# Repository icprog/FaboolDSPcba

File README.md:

#FABOOL Laser DS PCBA
- Product page: https://www.smartdiys.cc/fabool-laser-ds/
- Shop page: https://shop.smartdiys.cc/collections/80w-co2-laser-cutter-and-engraver

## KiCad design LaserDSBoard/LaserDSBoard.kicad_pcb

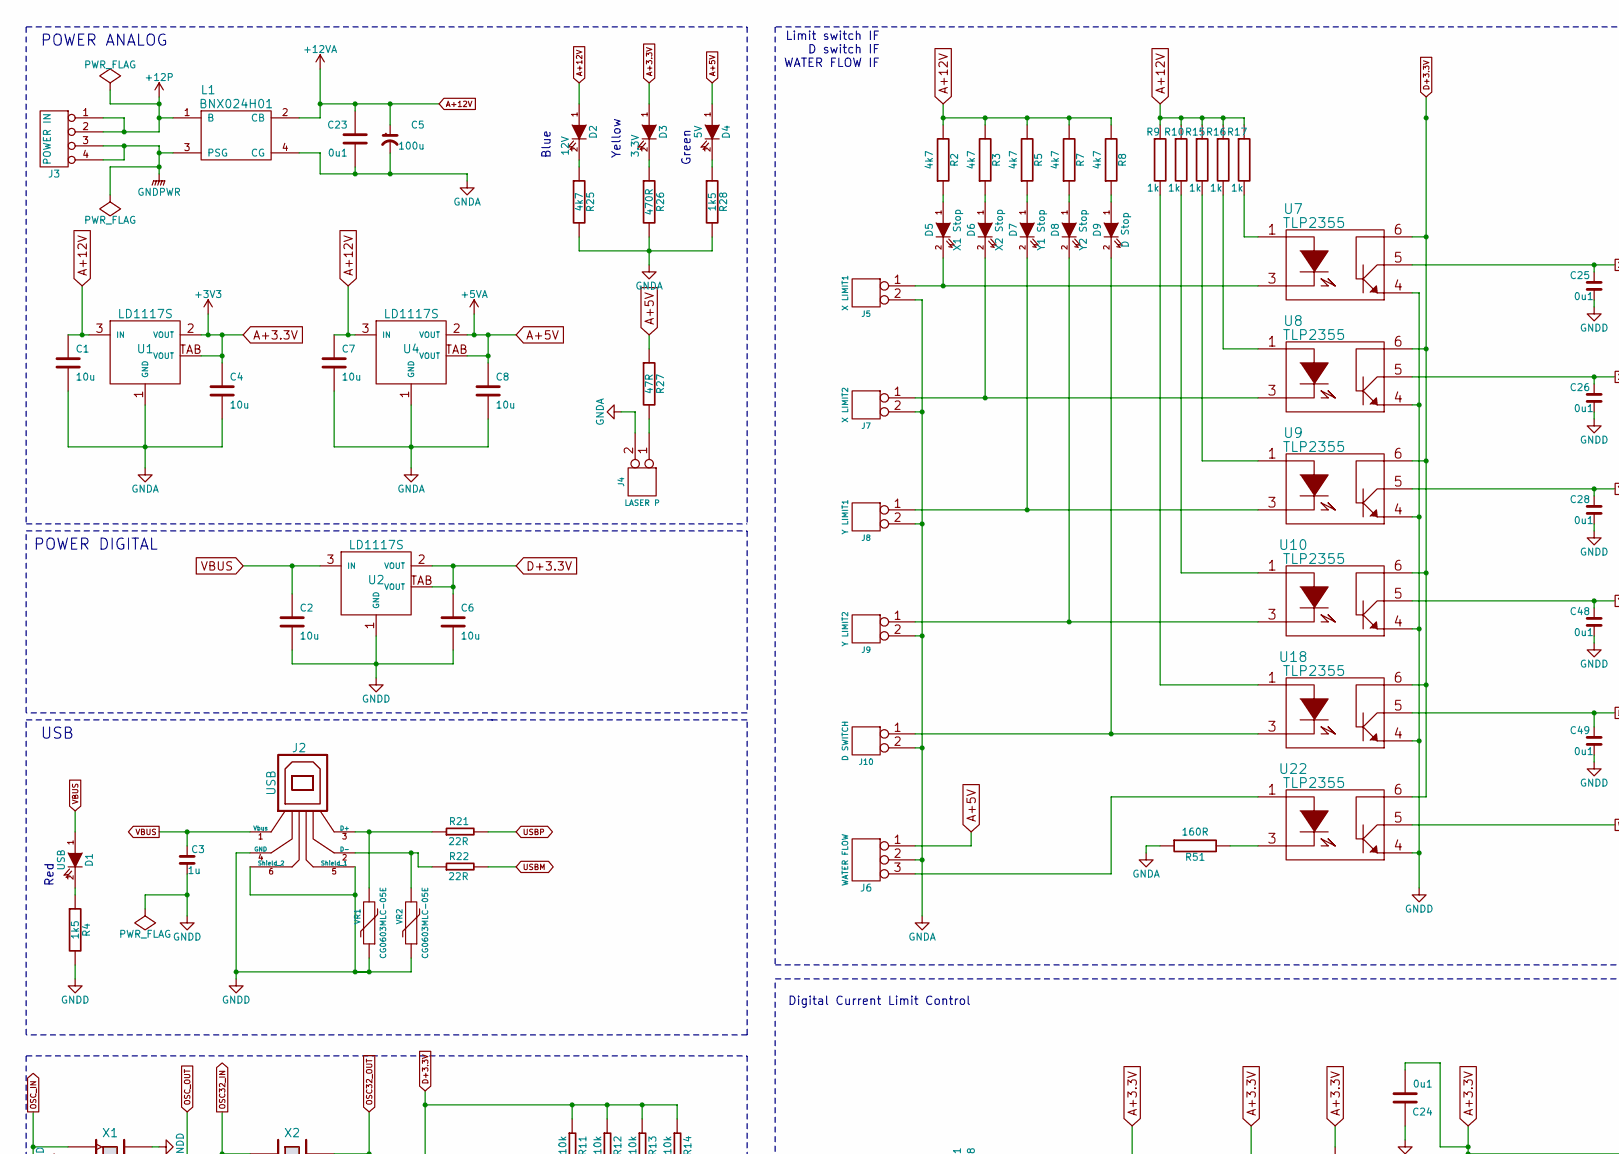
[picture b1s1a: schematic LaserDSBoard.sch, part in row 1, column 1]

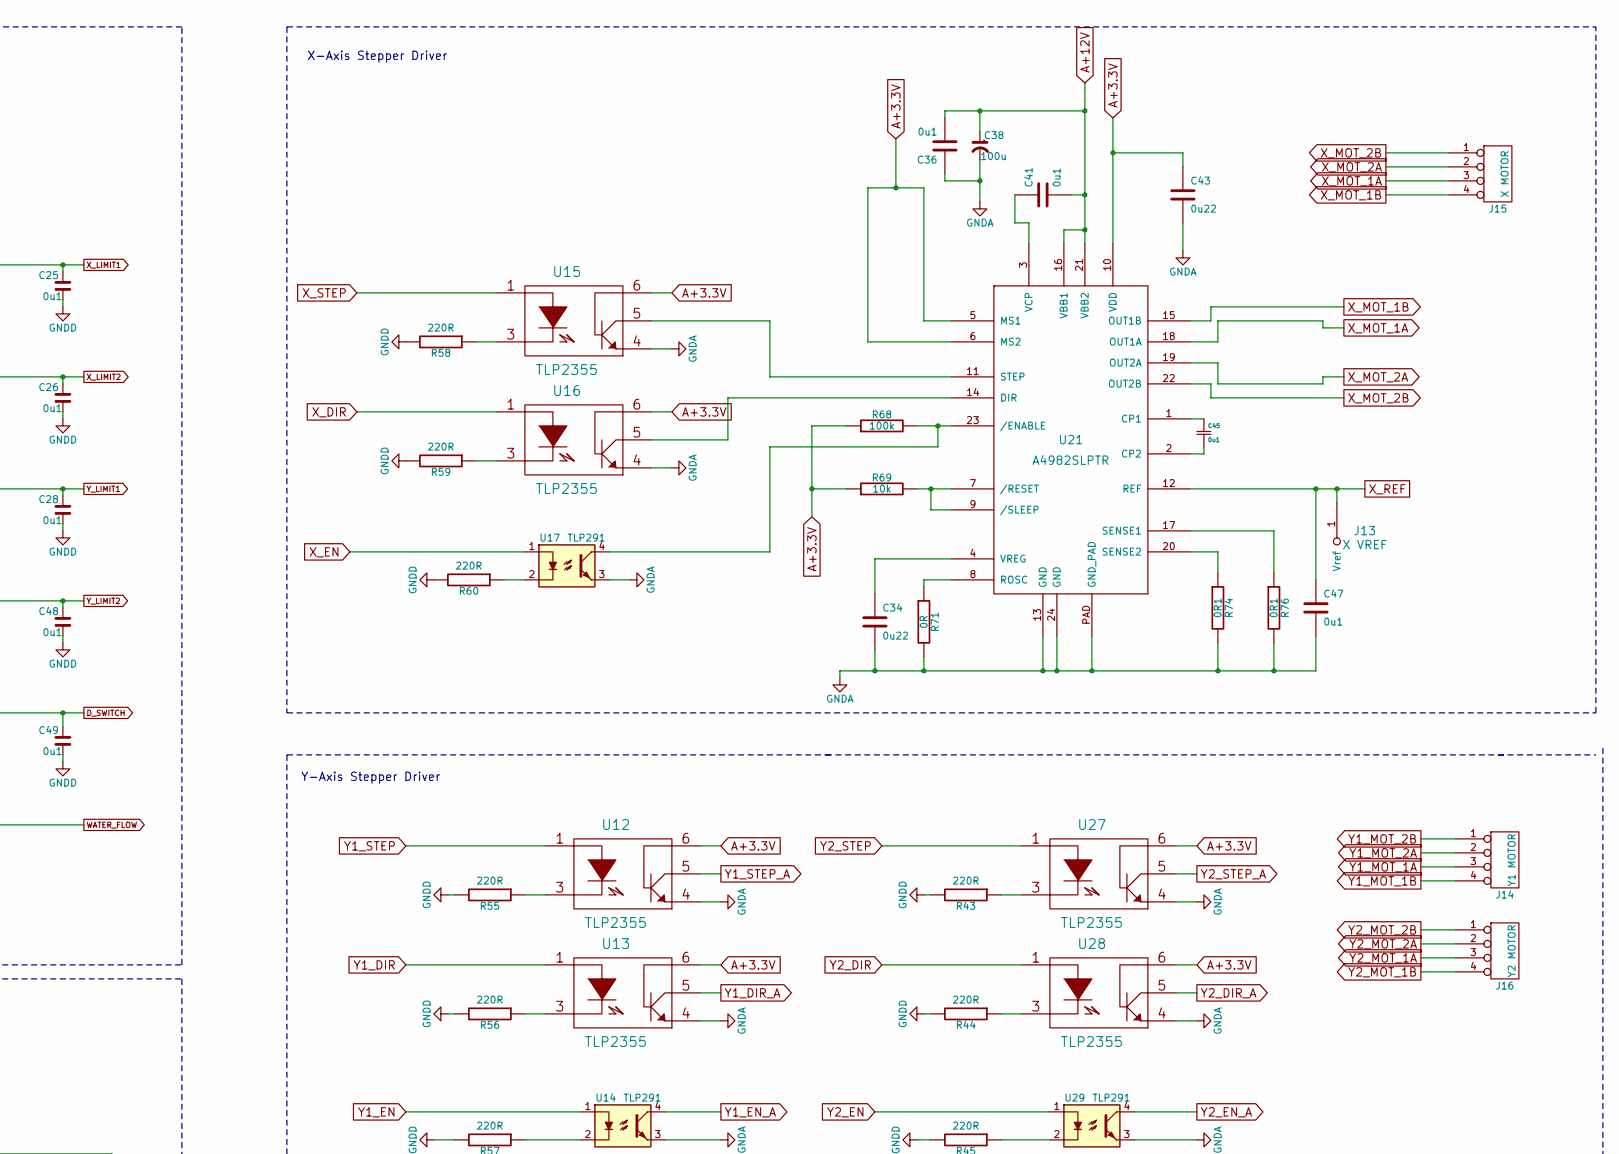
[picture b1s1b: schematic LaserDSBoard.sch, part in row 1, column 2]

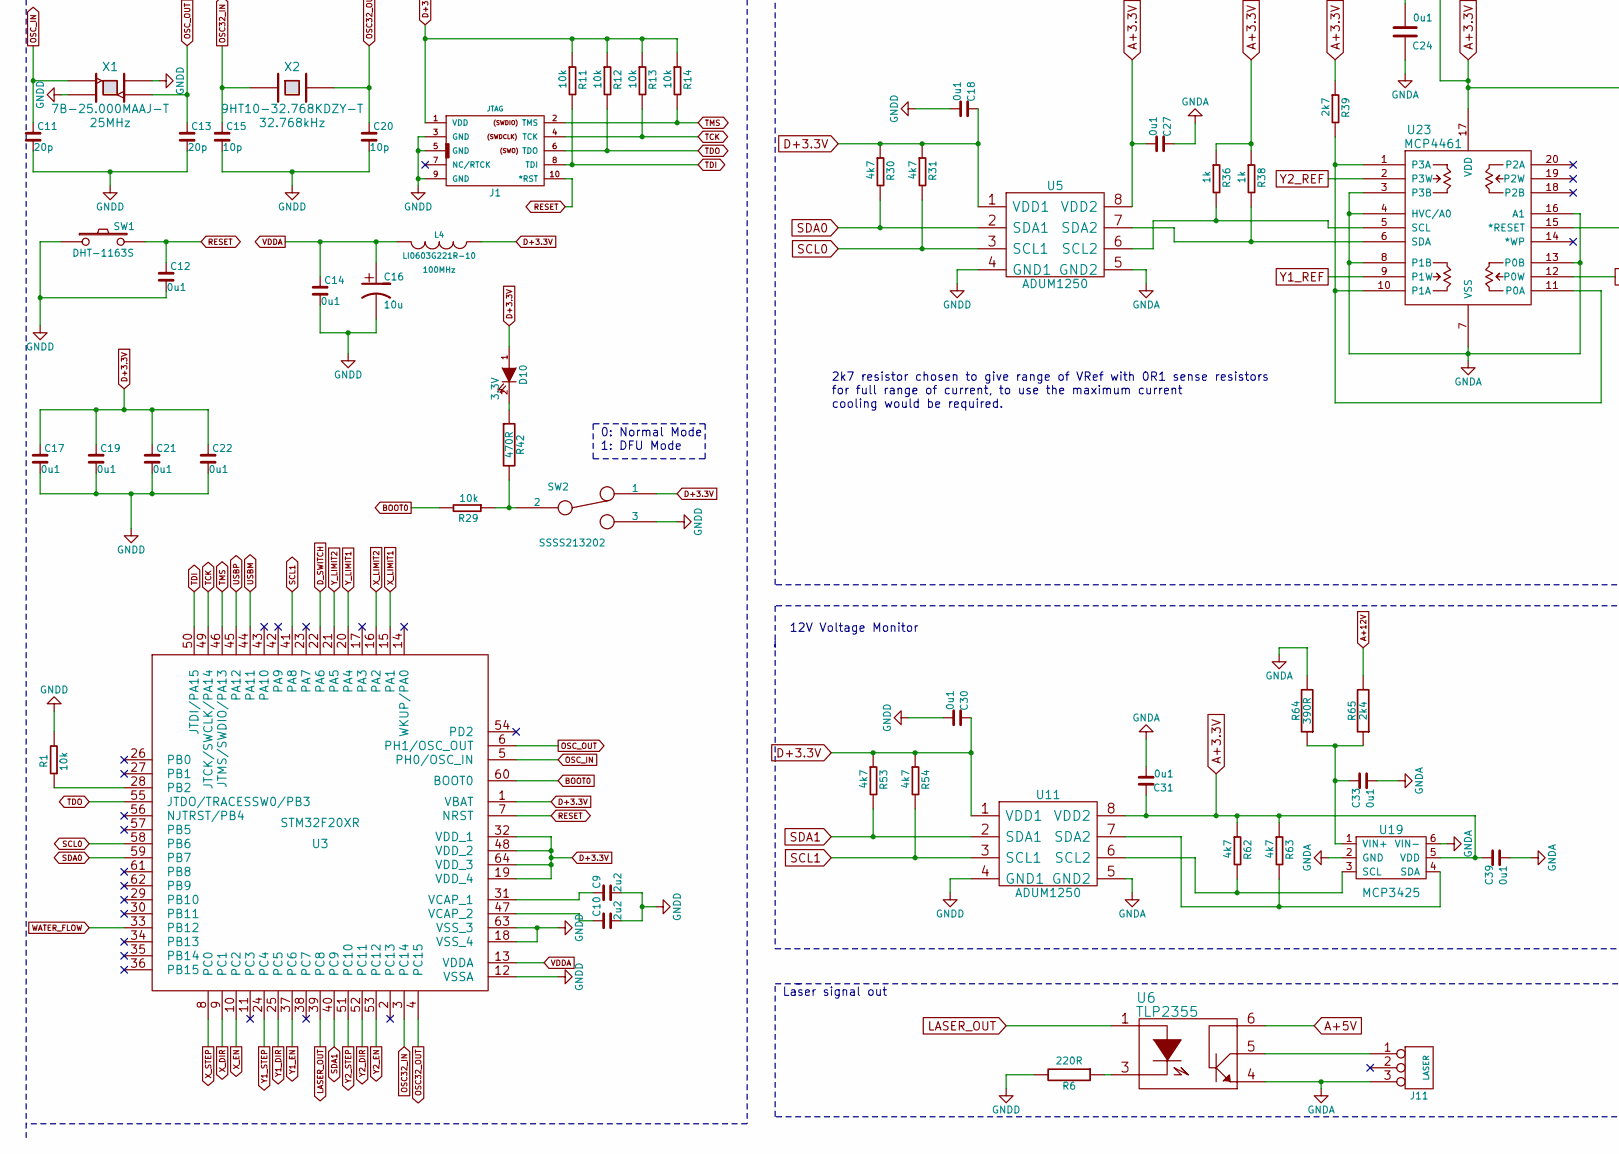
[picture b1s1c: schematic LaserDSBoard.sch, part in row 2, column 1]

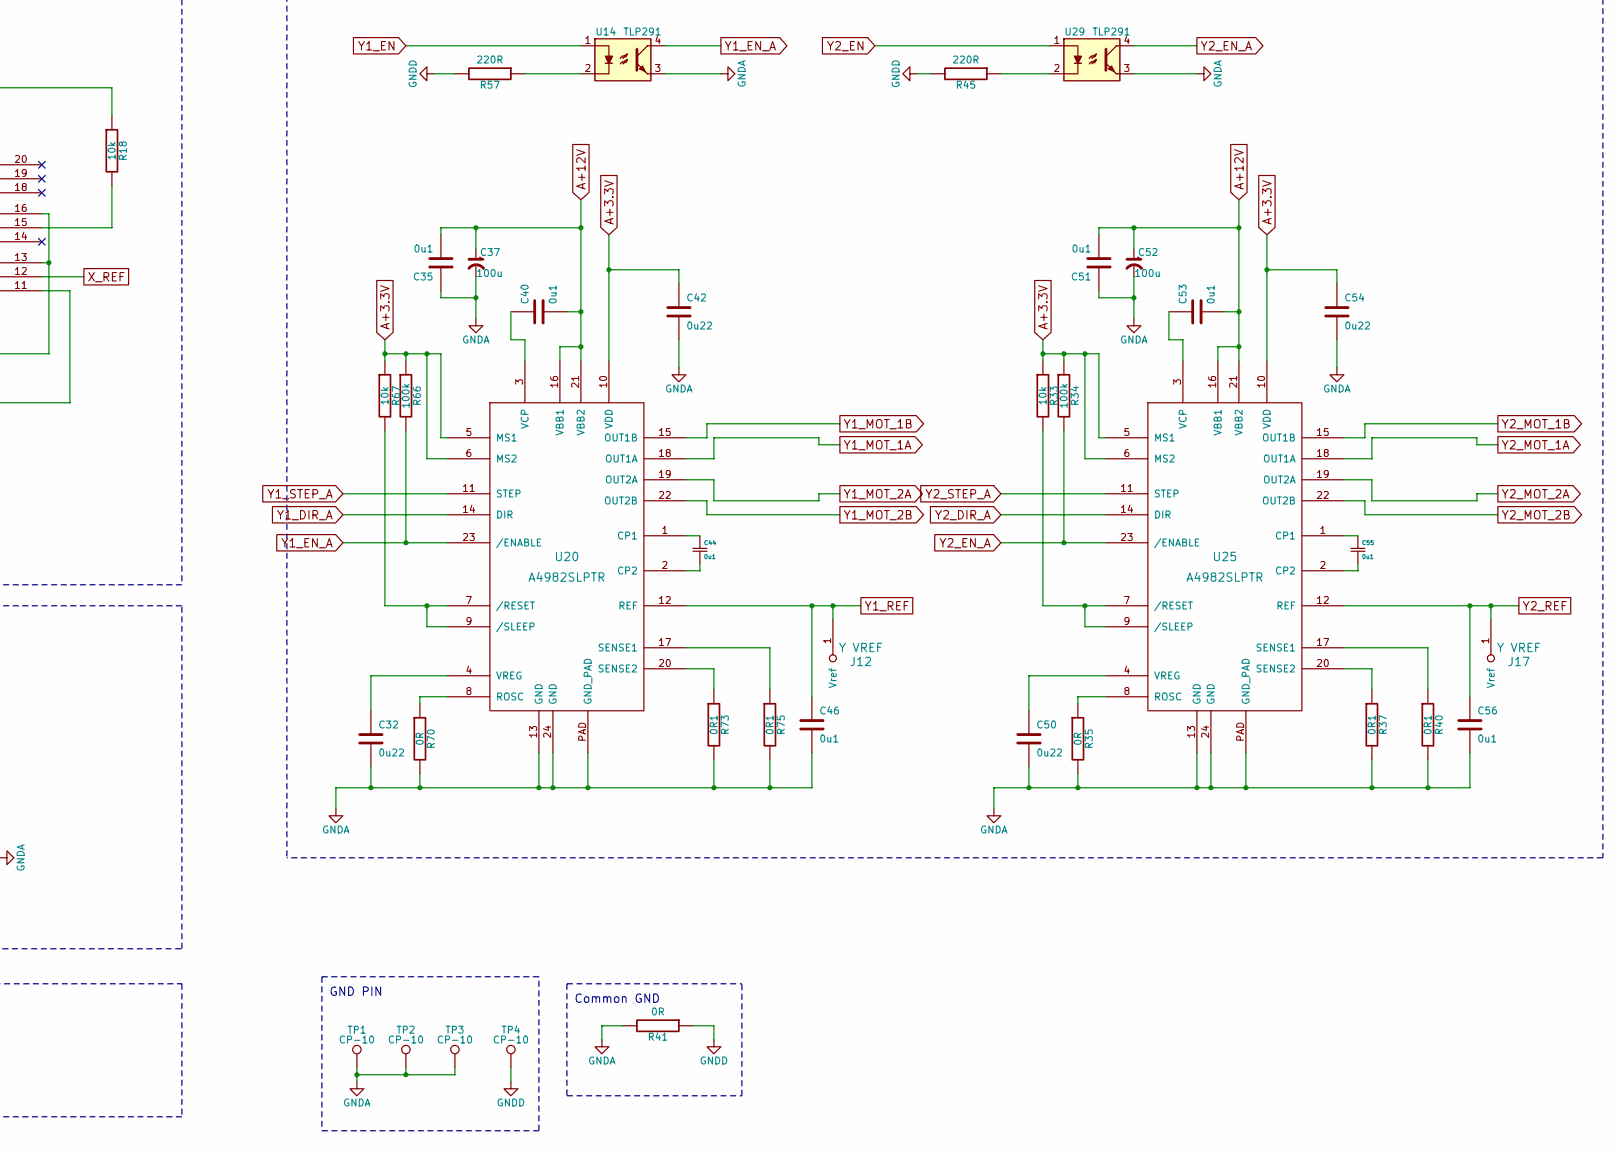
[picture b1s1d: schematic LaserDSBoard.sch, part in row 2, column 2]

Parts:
C1, C2, C4, C6, C7, C8, C16: 10u; C_0805
C3: 1u; C_0603
C5, C37, C38, C52: 100u; CP_Elec_6.3x7.7
C9, C10: 2u2; C_0603
C11, C13: 20p; C_0603
C12, C14, C17, C18, C19, C21, C22, C23, C24, C25, C26, C27, C28, C30, C31, C33, C35, C36, C39, C40, C41, C44, C45, C46, C47, C48, C49, C51, C53, C55, C56: 0u1; C_0805
C15, C20: 10p; C_0603
C32, C34, C42, C43, C50, C54: 0u22; C_0603
D1: USB; D_0805
D2: 12V; D_0805
D3, D10: 3.3V; D_0805
D4: 5V; D_0805
D5: X1 Stop; D_0805
D6: X2 Stop; D_0805
D7: Y1 Stop; D_0805
D8: Y2 Stop; D_0805
D9: D Stop; D_0805
J1: JTAG; Pin_Header_Straight_2x05_Pitch1.27mm
J2: USB; USB_B
J3: POWER IN; VH-4
J4: LASER P; B2B-XH-A
J5: X LIMIT1; B2B-XH-A
J6: WATER FLOW; B3B-XH-A
J7: X LIMIT2; B2B-XH-A
J8: Y LIMIT1; B2B-XH-A
J9: Y LIMIT2; B2B-XH-A
J10: D SWITCH; B2B-XH-A
J11: LASER; B3B-XH-A
J12, J17: Y VREF; Pin_Header_Straight_1x01_Pitch1.00mm
J13: X VREF; Pin_Header_Straight_1x01_Pitch1.00mm
J14: Y1 MOTOR; VH-4
J15: X MOTOR; VH-4
J16: Y2 MOTOR; VH-4
L1: BNX024H01
L4: LI0603G221R-10; R_0603
R1, R11, R12, R13, R14, R18, R29, R33, R67, R69: 10k; R_0603
R2, R3, R5, R7, R8, R25, R30, R31, R53, R54, R62, R63: 4k7; R_0603
R4, R28: 1k5; R_0603
R6, R43, R44, R45, R55, R56, R57, R58, R59, R60: 220R; R_1206
R9, R10, R15, R16, R17, R36, R38: 1k; R_0603
R21, R22: 22R; R_0603
R26, R42: 470R; R_0603
R27: 47R; R_0603
R34, R66, R68: 100k; R_0603
R35, R41, R70, R71: 0R; R_1206
R37, R40, R73, R74, R75, R76: 0R1; R_1206
R39: 2k7; R_0603
R51: 160R; R_1206
R64: 390R; R_0603
R65: 2k4; R_0603
SW1: DHT-1163S
SW2: SSSS213202
TP1, TP2, TP3, TP4: CP-10; Pin_Header_Straight_1x01_Pitch2.54mm
U1, U2, U4: LD1117S; LD1117S33TR
U3: STM32F20XR; LQFP-64_10x10mm_Pitch0.5mm
U5, U11: ADUM1250
U6, U7, U8, U9, U10, U12, U13, U15, U16, U18, U22, U27, U28: TLP2355
U14, U17, U29: TLP291; TLP291(SE
U19: MCP3425
U20, U21, U25: A4982SLPTR
U23: MCP4461; TSSOP-20_4.4x6.5mm_P0.65mm
VR1, VR2: CG0603MLC-05E; C_0603
X1: 7B-25.000MAAJ-T; Oscillator_SMD_Fordahl_DFAS15-4pin_5.0x3.2mm
X2: 9HT10-32.768KDZY-T; C_1206

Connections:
+12P: J3.1, J3.2, L1.1 (B)
A+3.3V: C4.1, C24.2, C27.2, C31.1, C39.1, C42.1, C43.1, C54.1, D3.1 (A), R18.1, R33.1, R34.1, R36.1, R38.1, R39.1, R62.1, R63.1, R66.1, R67.1, R68.1, R69.1, U1.2 (VOUT), U1.TAB (VOUT), U5.8 (VDD2), U11.8 (VDD2), U12.6, U13.6, U15.6, U16.6, U19.5 (VDD), U20.5 (MS1), U20.6 (MS2), U20.10 (VDD), U21.5 (MS1), U21.6 (MS2), U21.10 (VDD), U23.17 (VDD), U25.5 (MS1), U25.6 (MS2), U25.10 (VDD), U27.6, U28.6
A+5V: C8.1, D4.1 (A), J6.1, R27.1, U4.2 (VOUT), U4.TAB (VOUT), U6.6
A+12V: C1.1, C5.1, C7.1, C23.1, C35.2, C36.2, C37.1, C38.1, C40.2, C41.2, C51.2, C52.1, C53.2, D2.1 (A), L1.2 (CB), R2.2, R3.2, R5.2, R7.2, R8.2, R9.1, R10.1, R15.1, R16.1, R17.1, R65.2, U1.3 (IN), U4.3 (IN), U20.16 (VBB1), U20.21 (VBB2), U21.16 (VBB1), U21.21 (VBB2), U25.16 (VBB1), U25.21 (VBB2)
BOOT0: R29.2, U3.60 (BOOT0)
D+3.3V: C6.1, C17.1, C18.1, C19.1, C21.1, C22.1, C30.1, D10.1 (A), J1.1 (VDD), L4.1, R11.1, R12.1, R13.1, R14.1, R30.1, R31.1, R53.1, R54.1, SW2.1, U2.2 (VOUT), U2.TAB (VOUT), U3.1 (VBAT), U3.19 (VDD_4), U3.32 (VDD_1), U3.48 (VDD_2), U3.64 (VDD_3), U5.1 (VDD1), U7.6, U8.6, U9.6, U10.6, U11.1 (VDD1), U18.6, U22.6
D_SWITCH: C49.1, U3.22 (PA6), U18.5
GNDA: C1.2, C4.2, C5.2, C7.2, C8.2, C23.2, C24.1, C27.1, C31.2, C32.2, C33.2, C34.2, C35.1, C36.1, C37.2, C38.2, C39.2, C42.2, C43.2, C46.2, C47.2, C50.2, C51.1, C52.2, C54.2, C56.2, J4.2 (PM), J5.2 (PM), J6.2 (PM), J7.2 (PM), J8.2 (PM), J9.2 (PM), J10.2 (PM), J11.3, L1.4 (CG), R25.2, R26.2, R28.2, R35.2, R37.2, R40.2, R41.2, R51.1, R64.2, R70.2, R71.2, R73.2, R74.2, R75.2, R76.2, TP1.1, TP2.1, TP3.1, U1.1 (GND), U4.1 (GND), U5.5 (GND2), U6.4, U11.5 (GND2), U12.4, U13.4, U14.3, U15.4, U16.4, U17.3, U19.2 (GND), U19.6 (VIN-), U20.13 (GND), U20.24 (GND), U20.PAD (GND_PAD), U21.13 (GND), U21.24 (GND), U21.PAD (GND_PAD), U23.3 (P3B), U23.4 (HVC/A0), U23.7 (VSS), U23.8 (P1B), U23.13 (P0B), U23.16 (A1), U25.13 (GND), U25.24 (GND), U25.PAD (GND_PAD), U27.4, U28.4, U29.3
GNDD: C2.2, C3.2, C6.2, C9.2, C10.2, C11.2, C12.2, C13.2, C14.2, C15.2, C16.2, C17.2, C18.2, C19.2, C20.2, C21.2, C22.2, C25.2, C26.2, C28.2, C30.2, C48.2, C49.2, J1.3 (GND), J1.5 (GND), J1.9 (GND), J2.4 (GND), J2.5 (Shield_1), J2.6 (Shield_2), R1.2, R4.2, R6.2, R41.1, R43.2, R44.2, R45.2, R55.2, R56.2, R57.2, R58.2, R59.2, R60.2, SW1.1, SW2.3, TP4.1, U2.1 (GND), U3.12 (VSSA), U3.18 (VSS_4), U3.63 (VSS_3), U5.4 (GND1), U7.4, U8.4, U9.4, U10.4, U11.4 (GND1), U18.4, U22.4, VR1.1, VR2.1, X1.2, X1.4
GNDPWR: J3.3, J3.4, L1.3 (PSG)
LASER_OUT: U3.39 (PC8), U6.1
unnamed: C9.1, U3.31 (VCAP_1)
unnamed: C10.1, U3.47 (VCAP_2)
unnamed: C32.1, U20.4 (VREG)
unnamed: C33.1, R64.1, R65.1, U19.1 (VIN+)
unnamed: C34.1, U21.4 (VREG)
unnamed: C40.1, U20.3 (VCP)
unnamed: C41.1, U21.3 (VCP)
unnamed: C44.1, U20.1 (CP1)
unnamed: C44.2, U20.2 (CP2)
unnamed: C45.1, U21.1 (CP1)
unnamed: C45.2, U21.2 (CP2)
unnamed: C50.1, U25.4 (VREG)
unnamed: C53.1, U25.3 (VCP)
unnamed: C55.1, U25.1 (CP1)
unnamed: C55.2, U25.2 (CP2)
unnamed: D1.2 (K), R4.1
unnamed: D2.2 (K), R25.1
unnamed: D3.2 (K), R26.1
unnamed: D4.2 (K), R28.1
unnamed: D5.1 (A), R2.1
unnamed: D5.2 (K), J5.1, U7.3
unnamed: D6.1 (A), R3.1
unnamed: D6.2 (K), J7.1, U8.3
unnamed: D7.1 (A), R5.1
unnamed: D7.2 (K), J8.1, U9.3
unnamed: D8.1 (A), R7.1
unnamed: D8.2 (K), J9.1, U10.3
unnamed: D9.1 (A), R8.1
unnamed: D9.2 (K), J10.1, U18.3
unnamed: D10.2 (K), R42.1
unnamed: J2.2 (D-), R22.1, VR2.2
unnamed: J2.3 (D+), R21.1, VR1.2
unnamed: J4.1, R27.2
unnamed: J6.3, U22.1
unnamed: J11.1, U6.5
unnamed: R1.1, U3.28 (PB2)
unnamed: R6.1, U6.3
unnamed: R9.2, U18.1
unnamed: R10.2, U10.1
unnamed: R15.2, U9.1
unnamed: R16.2, U8.1
unnamed: R17.2, U7.1
unnamed: R18.2, U23.15 (*RESET)
unnamed: R29.1, R42.2, SW2.2
unnamed: R33.2, U25.7 (/RESET), U25.9 (/SLEEP)
unnamed: R35.1, U25.8 (ROSC)
unnamed: R36.2, U5.6 (SCL2), U23.5 (SCL)
unnamed: R37.1, U25.20 (SENSE2)
unnamed: R38.2, U5.7 (SDA2), U23.6 (SDA)
unnamed: R39.2, U23.1 (P3A), U23.10 (P1A), U23.11 (P0A)
unnamed: R40.1, U25.17 (SENSE1)
unnamed: R43.1, U27.3
unnamed: R44.1, U28.3
unnamed: R45.1, U29.2
unnamed: R51.2, U22.3
unnamed: R55.1, U12.3
unnamed: R56.1, U13.3
unnamed: R57.1, U14.2
unnamed: R58.1, U15.3
unnamed: R59.1, U16.3
unnamed: R60.1, U17.2
unnamed: R62.2, U11.6 (SCL2), U19.3 (SCL)
unnamed: R63.2, U11.7 (SDA2), U19.4 (SDA)
unnamed: R67.2, U20.7 (/RESET), U20.9 (/SLEEP)
unnamed: R68.2, U17.4, U21.23 (/ENABLE)
unnamed: R69.2, U21.7 (/RESET), U21.9 (/SLEEP)
unnamed: R70.1, U20.8 (ROSC)
unnamed: R71.1, U21.8 (ROSC)
unnamed: R73.1, U20.20 (SENSE2)
unnamed: R74.1, U21.20 (SENSE2)
unnamed: R75.1, U20.17 (SENSE1)
unnamed: R76.1, U21.17 (SENSE1)
unnamed: U15.5, U21.11 (STEP)
unnamed: U16.5, U21.14 (DIR)
OSC32_IN: C15.1, U3.3 (PC14), X2.1
OSC32_OUT: C20.1, U3.4 (PC15), X2.2
OSC_IN: C11.1, U3.5 (PH0/OSC_IN), X1.1
OSC_OUT: C13.1, U3.6 (PH1/OSC_OUT), X1.3
RESET: C12.1, J1.10 (*RST), SW1.2, U3.7 (NRST)
SCL0: R31.2, U3.58 (PB6), U5.3 (SCL1)
SCL1: R54.2, U3.41 (PA8), U11.3 (SCL1)
SDA0: R30.2, U3.59 (PB7), U5.2 (SDA1)
SDA1: R53.2, U3.40 (PC9), U11.2 (SDA1)
TCK: J1.4 (TCK), R13.2, U3.49 (JTCK/SWCLK/PA14)
TDI: J1.8 (TDI), R11.2, U3.50 (JTDI/PA15)
TDO: J1.6 (TDO), R12.2, U3.55 (JTDO/TRACESSW0/PB3)
TMS: J1.2 (TMS), R14.2, U3.46 (JTMS/SWDIO/PA13)
USBM: R22.2, U3.44 (PA11)
USBP: R21.2, U3.45 (PA12)
VBUS: C2.1, C3.1, D1.1 (A), J2.1 (Vbus), U2.3 (IN)
VDDA: C14.1, C16.1, L4.2, U3.13 (VDDA)
WATER_FLOW: U3.33 (PB12), U22.5
X_DIR: U3.9 (PC1), U16.1
X_EN: U3.10 (PC2), U17.1
X_LIMIT1: C25.1, U3.15 (PA1), U7.5
X_LIMIT2: C26.1, U3.16 (PA2), U8.5
X_MOT_1A: J15.3, U21.18 (OUT1A)
X_MOT_1B: J15.4, U21.15 (OUT1B)
X_MOT_2A: J15.2, U21.19 (OUT2A)
X_MOT_2B: J15.1, U21.22 (OUT2B)
X_REF: C47.1, J13.1, U21.12 (REF), U23.12 (P0W)
X_STEP: U3.8 (PC0), U15.1
Y1_DIR: U3.25 (PC5), U13.1
Y1_DIR_A: U13.5, U20.14 (DIR)
Y1_EN: U3.37 (PC6), U14.1
Y1_EN_A: R66.2, U14.4, U20.23 (/ENABLE)
Y1_MOT_1A: J14.3, U20.18 (OUT1A)
Y1_MOT_1B: J14.4, U20.15 (OUT1B)
Y1_MOT_2A: J14.2, U20.19 (OUT2A)
Y1_MOT_2B: J14.1, U20.22 (OUT2B)
Y1_REF: C46.1, J12.1, U20.12 (REF), U23.9 (P1W)
Y1_STEP: U3.24 (PC4), U12.1
Y1_STEP_A: U12.5, U20.11 (STEP)
Y2_DIR: U3.52 (PC11), U28.1
Y2_DIR_A: U25.14 (DIR), U28.5
Y2_EN: U3.53 (PC12), U29.1
Y2_EN_A: R34.2, U25.23 (/ENABLE), U29.4
Y2_MOT_1A: J16.3, U25.18 (OUT1A)
Y2_MOT_1B: J16.4, U25.15 (OUT1B)
Y2_MOT_2A: J16.2, U25.19 (OUT2A)
Y2_MOT_2B: J16.1, U25.22 (OUT2B)
Y2_REF: C56.1, J17.1, U23.2 (P3W), U25.12 (REF)
Y2_STEP: U3.51 (PC10), U27.1
Y2_STEP_A: U25.11 (STEP), U27.5
Y_LIMIT1: C28.1, U3.20 (PA4), U9.5
Y_LIMIT2: C48.1, U3.21 (PA5), U10.5

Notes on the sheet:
Blue
Green
2k7 resistor chosen to give range of VRef with 0R1 sense resistors for full range of current, to use the maximum current cooling would be required.
Digital Current Limit Control
Y-Axis Stepper Driver
X-Axis Stepper Driver
USB
Red
12V Voltage Monitor
Yellow
Limit switch IF D switch IF WATER FLOW IF
Laser signal out
POWER ANALOG
POWER DIGITAL
Common GND
GND PIN
0: Normal Mode 1: DFU Mode

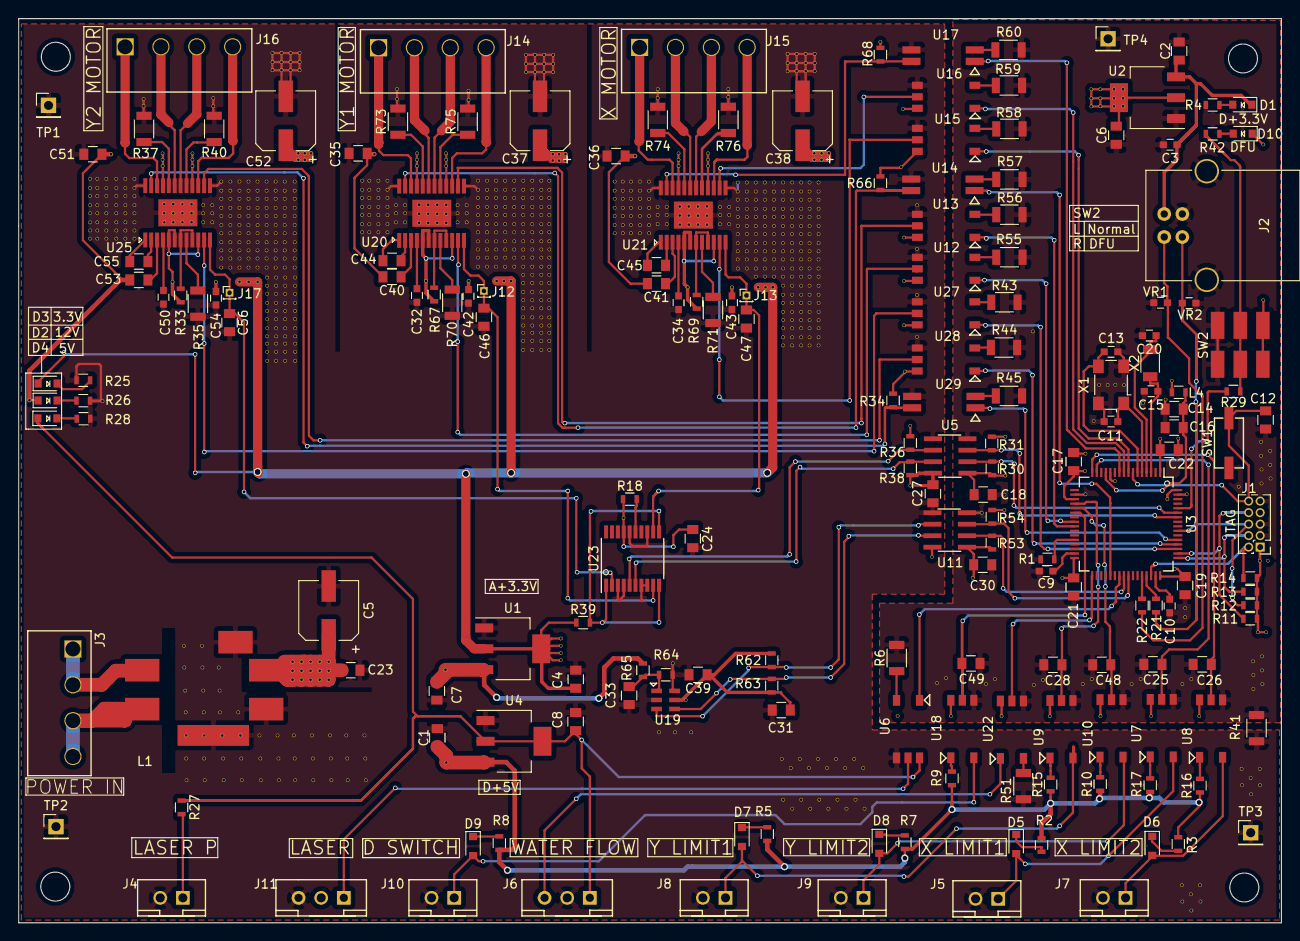
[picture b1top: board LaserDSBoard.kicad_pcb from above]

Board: 4 copper layers, 139.5 x 99.9 mm, 184 parts (0 on the bottom side), 137 nets.

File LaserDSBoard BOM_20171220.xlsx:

| Part / Value | Package | Manufacturer | Part No | Circuit Reference | Qty | URL
 | LD1117S33 | SOT-223 | STMicroelectronics | LD1117S33TR | U2,U1 | 2 | https://www.digikey.jp/product-detail/ja/stmicroelectronics/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
 | LD1117S50 | SOT-223 | STMicroelectronics | LD1117S50TR | U4 | 1 | https://www.digikey.jp/product-detail/ja/stmicroelectronics/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
 | 74HC08A | TSSOP-14 | ON Semiconductor | MC74HC08ADTR2G | U10 | 1 | http://www.digikey.jp/product-detail/ja/on-semiconductor/MC7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
 | 74HC1G00 | TSOP-5 | ON Semiconductor | MC74HC1G00DTT1G | U18 | 1 | http://www.digikey.jp/product-detail/ja/MC74HC1G00DTT1G/MC74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
 | MCP4461 | 20-TSSOP | Microchip Technology | MCP4461-103E/ST | U8 | 1 | http://www.digikey.jp/product-detail/ja/microchip-technology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
 | MCP3425 | SOT-23-6 | Microchip Technology | MCP3425A0T-E/CH | U19 | 1 | https://www.digikey.jp/product-detail/ja/microchip-technolog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
 | A4982 | 24-TSSOP | Allegro MicroSystems, LLC | A4982SLPTR | U21,U20 | 2 | http://www.digikey.jp/product-detail/ja/allegro-microsystems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
 | STM32F205 | 64-LQFP | STMicroelectronics | STM32F205RBT6 | U3 | 1 | http://www.digikey.jp/product-search/ja?keywords=STM32F205RBT6
 | ADUM1250ARZ-RL7 | 8-SOIC | Analog Devices Inc. | ADUM1250 | U5,U11 | 2
 | BSH105,215 | SOT-23 | NXP Semiconductors | BSH105 | TR1 | 1 | http://www.digikey.jp/product-detail/ja/nxp-semiconductors/BSH105,215/568-6215-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
 | TLP2355 | SO6 | TOSHIBA | TLP2355 | U17,U12,U16,U13,U15,U22,U14 | 7 | http://www.mouser.jp/ProductDetail/Toshiba/TLP2355TPLE/?qs=W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
 | TLP627 | 4-SMD | TOSHIBA | TLP627 | U7,U9 | 2
 | TLP627-4 | 16-DIP | TOSHIBA | TLP627-4 | U6 | 1 | https://www.digikey.jp/products/ja?keywords=TLP627-4
 | Tact Switch | DHT-1163S | D.O Electronics Co.,Ltd | DHT-1163S | SW1 | 1 | http://www.seeedstudio.com/depot/images/opl/datasheet/311020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
 | DIP Switch | MS-22D18 | DG De Yi Long Electronics Hardware Limited | MS-22D18 G2 | SW2 | 1 | http://www.seeedstudio.com/depot/images/opl/datasheet/301001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
 | Crystal
 | 25MHz, 18pF | 5032 | TXC CORPORATION | 7B-25.000MAAJ-T | X1 | 1 | http://www.digikey.jp/product-detail/ja/txc-corporation/7B-2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
 | RTC Crystal
 | 32.768KHz, 7pF | 2-SMD | TXC CORPORATION | 9HT10-32.768KDZY-T | X2 | 1 | http://www.digikey.jp/product-detail/ja/txc-corporation/9HT1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
 | ESD
 | VARISTOR 0603 | 0603 | Bourns Inc. | CG0603MLC-05E | VR1,VR2 | 2 | http://www.digikey.jp/product-detail/ja/bourns-inc/CG0603MLC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
 | Ferrite bead
 | 220Ω@100MHz, 700mA | 0603 | Laird-Signal Integrity Products | LI0603G221R-10 | L4 | 1 | http://www.digikey.jp/product-detail/ja/LI0603G221R-10/240-2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
 | 220Ω@100MHz, 2A | 0805 | Murata Electronics North America | BLM21PG221SN1D | L3 | 1 | http://www.digikey.jp/product-detail/ja/murata-electronics-n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
 | 30Ω@100MHz, 8.5A | 0805 | Murata Electronics North America | BLM21SN300SN1D | L1,L2 | 2 | http://www.digikey.jp/product-detail/ja/murata-electronics-n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
 | LED
 | 2V, 3mA, Red | 0805 | Any | Any | D1,D5,D6,D7,D8,D9 | 6
 | 2V, 3mA, Green | 0805 | Any | Any | D4 | 1
 | 2V, 3mA, Blue | 0805 | Any | Any | D2, | 1
 | 2V, 3mA, Yellow | 0805 | Any | Any | D3 | 1
 | Ceramic Capacitor
 | 10p, Ceramic, 10V, 10% | 0603 | Any | Any | C20,C15 | 2
 | 20p, Ceramic, 10V, 10% | 0603 | Any | Any | C13,C11 | 2
 | 0u1, Ceramic, 10V, 10% | 0603 | Any | Any | C25,C29,C23,C24,C47,C22,C46,C26,C45,C44,C12,C21,C17,C19,C27,C33,C28,C39,C31,C30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 | 21
 | 0u22, Ceramic, 10, 10% | 0603 | Any | Any | C43,C42,C32,C34 | 4
 | 2u2, Ceramic, 10V, 10% | 0603 | Any | Any | C10,C9 | 2
 | 1u, Ceramic, 10V, 10% | 0603 | Any | Any | C3 | 1
 | 0u1, Ceramic, 16V, 10% | 0805 | Any | Any | C40,C41,C35,C36,C14 | 5
 | 10u, Ceramic, 10V, 10% | 0805 | Any | Any | C7,C6,C8,C2,C4,C1 | 6
 | Tantalum Capacitor
 | 10uF, 10V, 20% | 1206 | Any | Any | C16 | 1
 | Aluminum Capacitor
 | 100u, 35V, 20% | 6.3 x 7.7mm | Any | Any | C5,C38,C37 | 3 | http://www.digikey.jp/product-detail/ja/UWT1V101MCL1GS/493-2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
 | Resistor
 | 0R, 1/10W | 0603 | Any | Any | R71,R70 | 2
 | 22R, 1/10W, 5% | 0603 | Any | Any | R21,R22 | 2
 | 47R, 1/10W, 5% | 0603 | Any | Any | R27 | 1
 | 100R, 1/10W, 5% | 0603 | Any | Any | R61 | 1
 | 220R, 1/10W, 5% | 0603 | Any | Any | R72,R57,R51,R55,R56,R60,R58,R59 | 8
 | 390R, 1/10W, 5% | 0603 | Any | Any | R64 | 1
 | 470R, 1/10W, 5% | 0603 | Any | Any | R26 | 1
 | 1k5, 1/10W, 5% | 0603 | Any | Any | R28,R4 | 2
 | 2k7, 1/10W, 5% | 0603 | Any | Any | R39 | 1
 | 4k7, 1/10W, 5% | 0603 | Any | Any | R63,R47,R46,R45,R35,R34,R33,R32,R37,R49,R40,R62,R48,R53,R54,R30,R31,R25,R38,R36 | 20
 | 10k, 1/10W, 5% | 0603 | Any | Any | R1,R69,R14,R13,R12,R11,R29,R52,R67 | 9
 | 100k, 1/10W, 5% | 0603 | Any | Any | R68,R66 | 2
 | 0R1, 1W, 5% | 1206 | Any | Any | R74,R76,R73,R75 | 4
 | 220R, 1/4W, 5% | 1206 | Any | Any | R8,R16,R10,R15,R17,R19,R23,R24,R20,R18,R2,R5,R7,R9,R3,R6 | 16
 | 1k, 1/4W, 5% | 1206 | Any | Any | R44,R43,R42,R41,R50 | 5
 | 1k5, 1/2W, 5% | 1206 | Any | Any | R65 | 1
 | Connector
 | USB Type B Connector | USB - B | Any | Any | J2 | 1 | http://www.digikey.jp/product-detail/ja/on-shore-technology-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
 | 2P Connector |  | JST Sales America Inc | B2B-XH-A(LF)(SN) | J3,J4,J5,J7,J8,J9,J10 | 7
 | 3P Connector |  | JST Sales America Inc | B3B-XH-A(LF)(SN) | J6,J11 | 2
 | 4P Connector |  | JST Sales America Inc | B4B-XH-A(LF)(SN) | J14,J15,J16 | 3
 | Other
 | Heat Sink |  | Shenzhen S-mart Electronics Co.,Ltd | Heatsink 8.8*8.8*5mm with 3m thermal conductivity double-sided tape |  | 2

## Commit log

2017-12-22 :lollipop: Added .gitattributes
2018-02-21 DSコントロール基板改版
    ・2→4層化
    ・Y軸モータードライバ増設(1→2)
    ・コネクタ変更
    ・デジタルポテンショメータ変更
2018-04-10 ver 2.0
    - DFUモード用のLEDを追加
    -フォトカプラ改修(GND接続)
    - R28 R4 R65 パッドサイズを0603に変更
    - 部品表 1k パッドサイズ1206→0603
    -TPL0401 PADピッチ誤り修正（TO-SOT23-6→カスタムPAD）
    -TP穴径変更
2018-05-11 Ver2.0.0
    [schematic]
    ・デジタルポテンショメータ MCP4461に戻す
    ・フォトカプラ ENの経路(U14,U17,U29)
    TLP2355→TLP291に変更
    [AW]
    ・回路図変更に伴うAW変更
2018-05-30 Ver2.0.1
    ・WATER FLOW 電源をA+3.3V→A+5.0Vにつなぎ変え
    ・R51 抵抗値変更
    220Ω→160Ω
2018-05-30 Ver2.0.1
    BOM修正(MCP4461 個数修正)
2018-06-04 Ver2.0.1
    ガーバーデータに実装用XY座標データ(.pos)を追加
    それに伴いガーバーデータのタイムスタンプ更新(内容は前pushと変更なし)
2018-08-08 Create LICENSE
2018-10-25 Ver2.0.2
    部品表更新
    20180607 → 20181025
